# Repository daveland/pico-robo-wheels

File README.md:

# RoboWheels
This Project will control up to 4 DC servomotors on a robot platform.  The code runs on an RPI pico and uses PWM to perform Speed control of DC motors.  The Pico PIO blocks are used to monitor Quadrature  encoders for motor Speed and position sensing.  Closed loop Velocity control is performed on each motor with Pairs velocity locked to each other for electronic differential mode.  This make the platfor Track straight when 2 motors are determining direction.

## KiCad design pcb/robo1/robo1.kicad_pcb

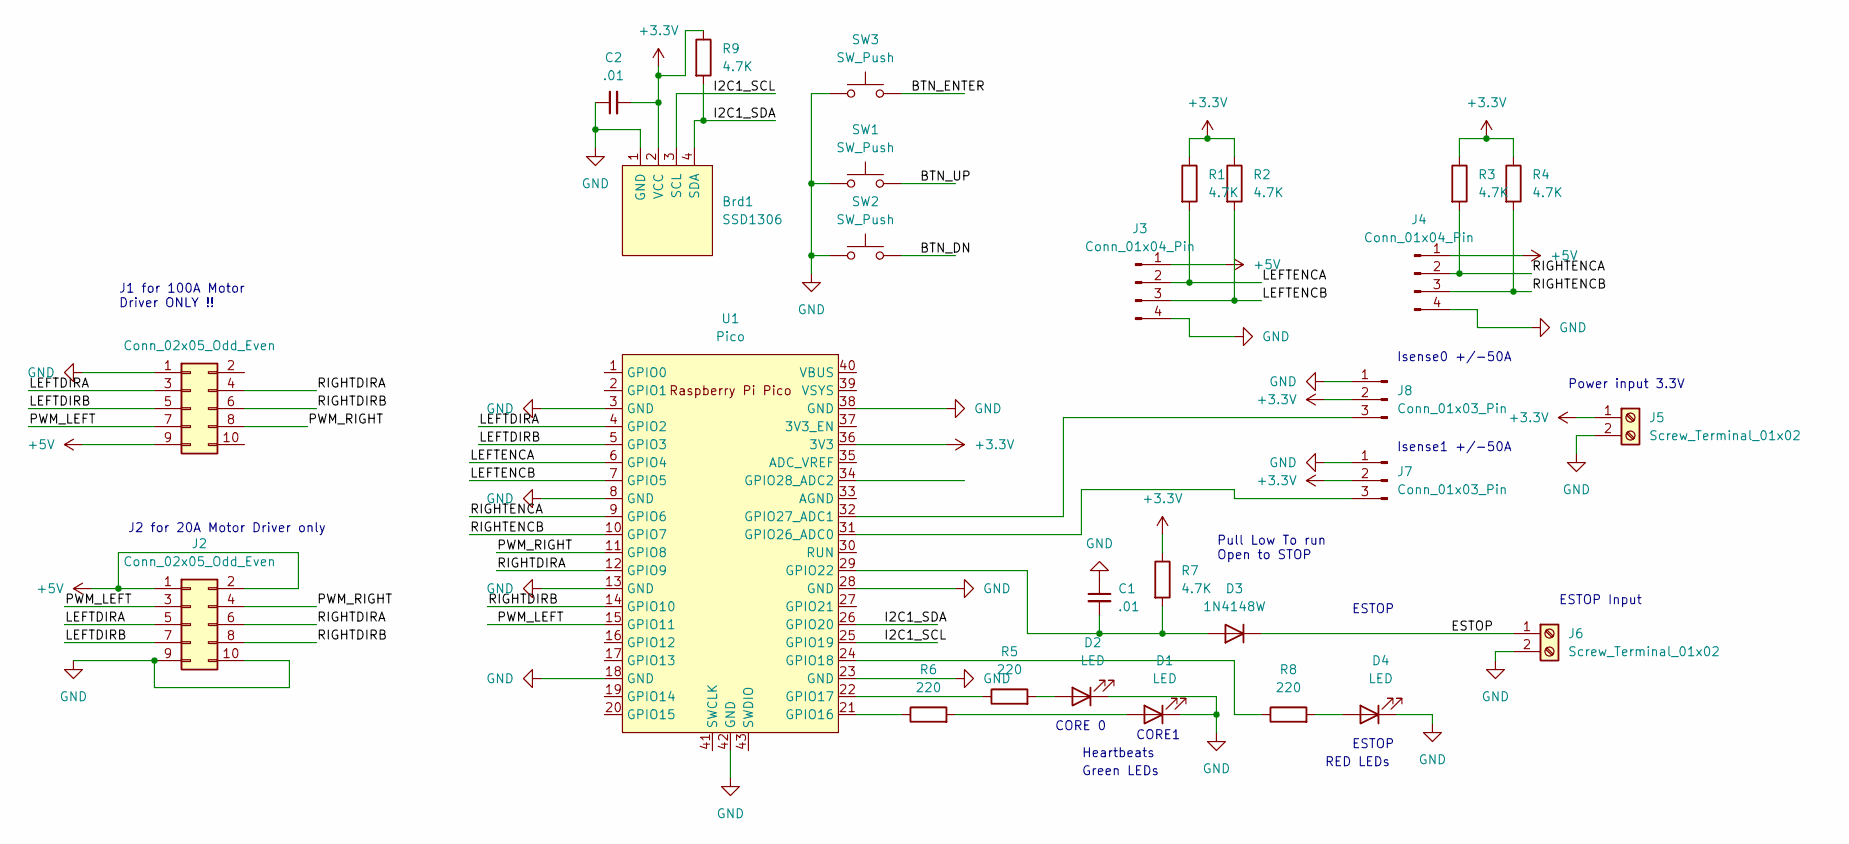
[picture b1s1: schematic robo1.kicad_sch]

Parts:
Brd1: SSD1306; 128x64OLED
C1, C2: .01; C_0603_1608Metric_Pad1.08x0.95mm_HandSolder
D1, D2, D4: LED; LED_1206_3216Metric_Pad1.42x1.75mm_HandSolder
D3: 1N4148W; D_SOD-123
J1, J2: Conn_02x05_Odd_Even; PinHeader_2x05_P2.54mm_Vertical
J3, J4: Conn_01x04_Pin; PinHeader_1x04_P2.54mm_Vertical
J5, J6: Screw_Terminal_01x02; TerminalBlock_bornier-2_P5.08mm
J7, J8: Conn_01x03_Pin; PinHeader_1x03_P2.54mm_Vertical
R1, R2, R3, R4, R7, R9: 4.7K; R_0201_0603Metric_Pad0.64x0.40mm_HandSolder
R5, R6, R8: 220; R_0201_0603Metric_Pad0.64x0.40mm_HandSolder
SW1, SW2, SW3: SW_Push; SW_PUSH_6mm
U1: Pico; RPi_Pico_SMD_TH

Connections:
+3.3V: Brd1.2 (VCC), C2.2, J5.1, J7.2, J8.2, R1.1, R2.1, R3.1, R4.1, R7.1, R9.1, U1.36 (3V3)
+5V: J1.9, J2.1, J2.2, J3.1, J4.1
/BTN_DN: SW2.2
/BTN_ENTER: SW3.2
/BTN_UP: SW1.2
/ESTOP: D3.1 (K), J6.1
/I2C1_SCL: Brd1.3 (SCL), U1.25 (GPIO19)
/I2C1_SDA: Brd1.4 (SDA), R9.2, U1.26 (GPIO20)
/LEFTDIRA: J1.3, J2.5, U1.4 (GPIO2)
/LEFTDIRB: J1.5, J2.7, U1.5 (GPIO3)
/LEFTENCA: J3.2, R1.2, U1.6 (GPIO4)
/LEFTENCB: J3.3, R2.2, U1.7 (GPIO5)
/PWM_LEFT: J1.7, J2.3, U1.15 (GPIO11)
/PWM_RIGHT: J1.8, J2.4, U1.11 (GPIO8)
/RIGHTDIRA: J1.4, J2.6, U1.12 (GPIO9)
/RIGHTDIRB: J1.6, J2.8, U1.14 (GPIO10)
/RIGHTENCA: J4.2, R3.2, U1.9 (GPIO6)
/RIGHTENCB: J4.3, R4.2, U1.10 (GPIO7)
GND: Brd1.1 (GND), C1.1, C2.1, D1.1 (K), D2.1 (K), D4.1 (K), J1.1, J2.9, J2.10, J3.4, J4.4, J5.2, J6.2, J7.1, J8.1, SW1.1, SW2.1, SW3.1, U1.3 (GND), U1.8 (GND), U1.13 (GND), U1.18 (GND), U1.23 (GND), U1.28 (GND), U1.38 (GND), U1.42 (GND)
unnamed: D1.2 (A), R6.2
unnamed: D2.2 (A), R5.2
unnamed: C1.2, D3.2 (A), R7.2, U1.29 (GPIO22)
unnamed: D4.2 (A), R8.2
unnamed: J7.3, U1.31 (GPIO26_ADC0)
unnamed: J8.3, U1.32 (GPIO27_ADC1)
unnamed: R6.1, U1.21 (GPIO16)
unnamed: R5.1, U1.22 (GPIO17)
unnamed: R8.1, U1.24 (GPIO18)

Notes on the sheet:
ESTOP Input
J2 for 20A Motor Driver only
ESTOP
Isense0 +/-50A
Isense1 +/-50A
Heartbeats
Pull Low To run Open to STOP
Green LEDs
Power input 3.3V
J1 for 100A Motor Driver ONLY !!
CORE1
CORE 0
RED LEDs

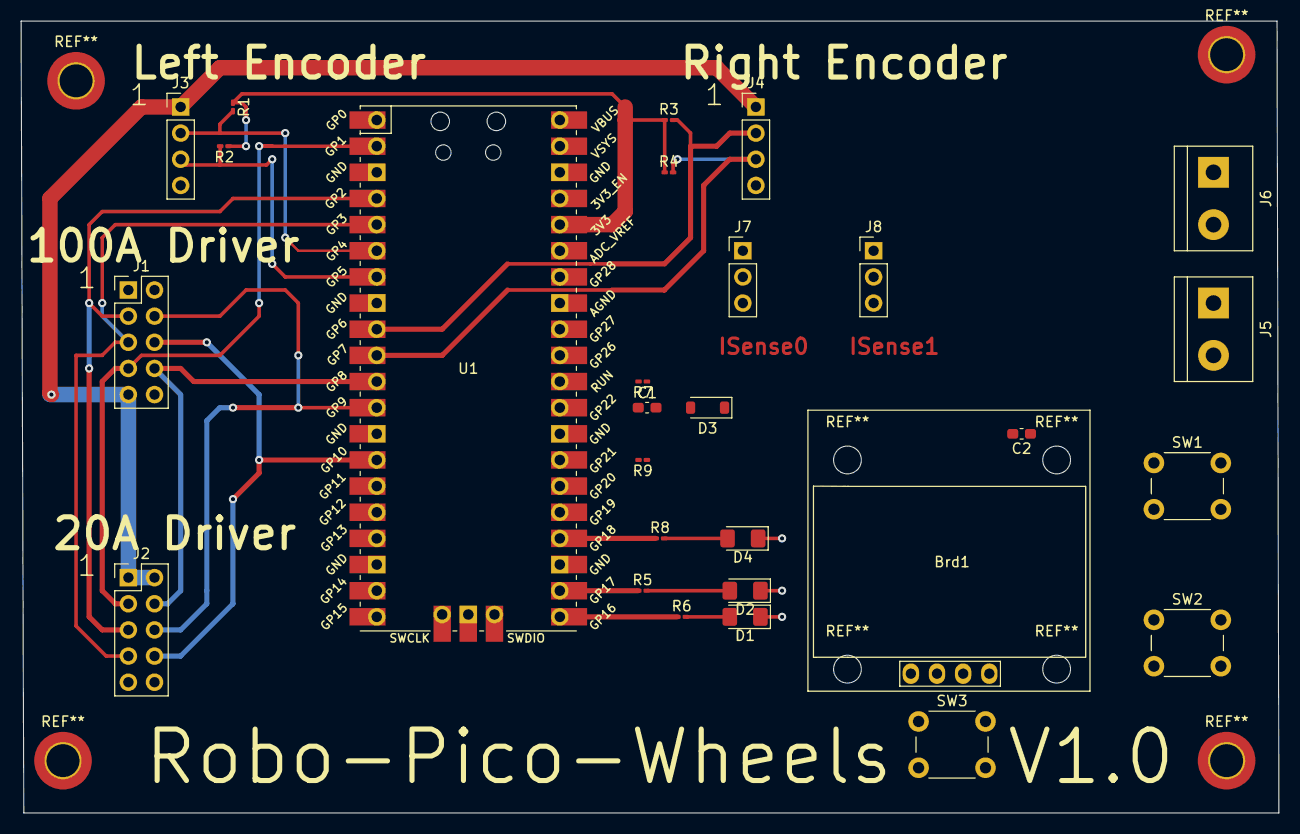
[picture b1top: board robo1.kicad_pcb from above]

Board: 2 copper layers, 122.2 x 76.9 mm, 28 parts (0 on the bottom side), 25 nets.

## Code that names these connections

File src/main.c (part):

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// Each pair must be adjacent  A+1=B
//Left encoder PIO0 block SM0  and Right encoder PIO1 block SM0
// We load same PIO code into both PIO blocks memory
const int LeftEncA =4; // use 2 pio blocks for now... Should be able to move to one PIO Block
const int LeftEncB =5;  // interrupts are not working like I expect to have 2 "copies" of the same 
const int RightEncA =6; // PIO Program Running on two SM's in the same PIO block and having unique 
const int RightEncB =7; // interrupts to call the count up/down IRQ's 
// seperatly Running on 2 pio blocks solves this for now


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        // state machine 0
        uint8_t sm = 0;
        // configure the used pins as input with pull up
        pio_gpio_init(pio, LeftEncA);
        gpio_set_pulls(LeftEncA, true, false);
        pio_gpio_init(pio, LeftEncB);
        gpio_set_pulls(LeftEncB, true, false);
        // load the pio program into the pio memory
         PIOoffset = pio_add_program(pio, &pico_robo_wheels_program);
        // make a sm config
        pio_sm_config c = pico_robo_wheels_program_get_default_config(PIOoffset);
        // set the 'in' pins
        sm_config_set_in_pins(&c, LeftEncA);
        // set shift to left: bits shifted by 'in' enter at the least
        // significant bit (LSB), no autopush
        sm_config_set_in_shift(&c, false, false, 0);
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        uint8_t sm = 0;
        // configure the used pins as input with pull up
       
        pio_gpio_init(pio, RightEncA);
        gpio_set_pulls(RightEncA, true, false);
        pio_gpio_init(pio, RightEncB);
        gpio_set_pulls(RightEncB, true, false);
        
        // load the pio program into the pio memory
        uint offset = pio_add_program(pio, &pico_robo_wheels_program);
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        pio_sm_config c = pico_robo_wheels_program_get_default_config(offset);
        // set the 'in' pins
       
        sm_config_set_in_pins(&c, RightEncA);
        // set shift to left: bits shifted by 'in' enter at the least
        // significant bit (LSB), no autopush
        sm_config_set_in_shift(&c, false, false, 0);
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
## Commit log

2024-06-02 Added docs
    XLS for model and Doc for overview and API
2024-06-02 Update README.md
    new description
2024-06-23 First Serial version
    Working serial. Lots of debug code. still more work to add commands and start Controls
2024-06-24 added DOCs removed printf debug
2024-07-06 update Core1 and PIO
    Pio for encoder services 2 SM machines, updated xls docs
2024-07-06 Core 1 running , pwm uncheacked
    Core1 booted and counting. encoder interrupts enabled, need to check them
2024-07-08 Put right encoder on PIO1
    Using both PIO's for encoders
    might be able to recode for one PIO Block
2024-07-19 add speed calcs to core 1
2024-07-27 Update Velocity calcs
2024-07-27 Add comments on core separation
2024-07-27 updated board id
2024-07-27 V0.2.2 Pushed pins for MTR A/B
    Moved Pins on Encoder and motor to remove DIR signal and change to MTRA and MTR B signal
2024-07-29 added cmds, mtr dir
    added FW,RT,LT,ST,TV, and PW cmds
2024-08-04 debugged duty sysle
2024-08-04 PW command in Decimal pct
    PW,35 sets both PWM chan values to 35%
    1% resolution
2024-09-01 add spinlocks to core 1 globals
    Try spinlocks on global data that core 1 modifies to core 0..
    \\no spinlokcks added for data going from core 0 to core 1
2024-09-03 add kicad pcb
    Kicad pcb added
2024-09-03 add kicad git ignore
2024-09-03 pcb outline
    added mounting holes and text labels
2024-09-24 Add OLED to PCB
    OLED added to pcb
2024-09-25 PCB added Isense connectors
2024-10-02 add oled
2024-10-18 first rp2350 branch
2024-10-19 json
2024-10-19 this should compile.. when I get rp2350 cpu setup right
2024-11-03 remove free rtos submodule
2024-11-05 add rpi pico flavor free rtos
2024-11-05 freee rtos config
2024-11-05 Runs on RP2350 --
    Must run Board configure and answer no !!!!
2024-11-16 update C stds
2024-11-16 version 0.2.9

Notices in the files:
src/main.c:
Copyright (C) 2024 {David L. Anderson} - All Rights Reserved
